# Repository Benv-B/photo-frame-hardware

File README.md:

# AirDrop ChLCD Photo Frame — Hardware

Open-source carrier board for a **ChLCD color e-paper frame with native iPhone AirDrop**.

The design connects a **XIAO ESP32-C5** to an **IRIS AW1005S102 panel and matching TCON**. It includes an NFC wake circuit, power latching and a three-AA battery input. NFC wakes the electronics; the photo is transferred through AirDrop.

- [Firmware and project introduction](https://github.com/Benv-B/ESP32Drop)
- [KiCad project and assembly notes](hardware/iris_xiao_c5_revC) — use KiCad 10.0.6 or a compatible newer version.
- [Schematic PDF](hardware/iris_xiao_c5_revC/output/IRIS_C5_RevC_schematic.pdf) · [BOM](hardware/iris_xiao_c5_revC/output/BOM.csv) · [Gerbers](hardware/iris_xiao_c5_revC/output/gerbers)

The prototype has displayed photos received through AirDrop. Battery runtime and the complete NFC wake → display → shutdown cycle still need validation. Read the assembly notes for FPC orientation and the JP1 battery/USB configuration.

Original carrier design: [CERN-OHL-P-2.0](LICENSE). Project scripts: [0BSD](LICENSES/0BSD.txt). [Third-party library credits](THIRD_PARTY_NOTICES.md). IRIS panel/TCON internals, vendor firmware and waveforms are not included. Development and documentation were assisted by AI.

## 中文

这是 **AirDrop ChLCD 彩色电子纸相框**的自制载板：XIAO ESP32-C5 主控，连接 IRIS 屏幕和配套 TCON，带 NFC 唤醒、电源锁存和三节 AA 电池输入。

**KiCad、原理图、BOM、Gerbers 和配套固件均已开放。** 样机已完成 AirDrop 照片显示；续航和完整唤醒/断电流程仍需验证。ChLCD 属于胆甾相液晶显示，与 Spectra 6 的电泳技术不同。

装配前请看[接线说明](hardware/iris_xiao_c5_revC/README.md)。本仓库开源自制载板，不包含商用屏幕/TCON 内部固件和波形。

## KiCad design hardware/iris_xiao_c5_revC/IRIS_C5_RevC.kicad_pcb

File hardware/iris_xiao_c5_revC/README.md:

## 用户改线后重新铺铜（2026-10-16）

当前 PCB 使用用户确认保存的主文件（2026-10-16 18:33:46），已由 KiCad 10.0.6 重新填充正、背面 GND 区。

635 个走线/过孔对象、66 个封装的位置及所有铜几何参数在铺铜前后一致；只重新计算铜区填充。H1–H4 另补充“仅 PCB 机械元素”属性，解决机械孔不属于原理图符号的提示，孔位和尺寸未变。DRC、未连接、原理图一致性问题均为 0，225 个电气引脚核对通过。详见 `output/pcb/copper_fill_audit.json`。

本次上传工程请使用 **KiCad 10.0.6 或更新兼容版本**。下文关于 KiCad 9 的描述是原始生成过程记录。正反面预览和 Gerber/钻孔文件已随当前板图重新导出；标准器件模型取自本机 KiCad 库，未提供模型的器件（含 XIAO）只显示焊盘。

# IRIS 智能相框载板 · Rev C

2026-10-16。三节一次性碱性 AA、XIAO ESP32-C5、用户已有 IRIS TCON 与39针排线，指定 FH26W-39S-0.3SHW(60) 连接器。RevC按用户确认改用 TPS61023，取消 PG 检测，保留 NFC 唤醒、电源保持和自动关机。RevB 工程保留在相邻目录。

## 本版改变

- U1 换为 **TPS61023DRLR / C919459**，六脚 SOT-563，同步升压、EN控制、真正关断。
- U3 换为 **NT3H2111W0FHKH / C710403**，XQFN8、1.6×1.6mm，中心金属区域不焊接。八个功能脚编号与原版本相同。
- 删除 PG 拉高电阻 R3、总线门控晶体管 Q6、PG 电平转换 Q8/R17。XIAO 的 D2/GPIO25 留空。
- U2.ON直接接 EN_LATCH；R15保持总线默认断开，Q7只由固件 BUS_EN 控制。没有追加电压检测芯片。
- R1=787kΩ/0.1%，R2=100kΩ/0.1%；L1改为顺络MWSA0518S-1R0MT（1µH，C408343）。PWM标称输出5.278V，PFM标称约5.33V，因此图中写“约5.3V”。电源网络名仍使用 `5V_BOOST`/`5V_SYS`，不是精确5.000V标称。

三张 A4 原理图按电源、NFC锁存、主控/FPC分组，组内直接连线、跨组网络标签。62个实体元件，较RevB减少4件。RevC属于电路修订，不能把其网表称为与RevB完全一致。

## 文件入口

- `IRIS_C5_RevC.kicad_pro`：保存的板图需 KiCad 10.0.6 或更新兼容版本，打开已有原理图无需运行生成脚本。
- `output/IRIS_C5_RevC_schematic.pdf`：三页原理图。
- `output/BOM.csv`：元件参数和封装；`PROCUREMENT.md`：采购证据及尚未锁定的物料。
- `output/native_netlist.xml`、`output/pin_connections.csv`：实际网表及逐引脚连接。
- `output/validation.json`、`output/ERC.json`：原生网表与设计清单核对、ERC结果。
- `output/revision_comparison.json`：与RevB相比的预期变更审计。
- `output/preview/`：原理图逐页渲染。
- `IRIS_C5_RevC.kicad_pcb`：已完成布线的双层 PCB，80×60mm；四个3.2mm非金属化安装孔。
- `output/pcb/board_top.png` / `board_bottom.png`：PCB 预览；不含未提供的器件三维模型。
- `output/pcb/top_copper.png` / `bottom_copper.png`：正、背面铜层与丝印，背面按翻板视角显示。
- `output/pcb/DRC.json` / `netlist_parity.json`：最终PCB检查与原理图逐引脚一致性报告。
- `output/gerbers/`：双层制板、钢网和PTH/NPTH钻孔文件，供首版样机使用。

## PCB 与装配

XIAO在左上，USB朝上板边；39针FPC在右边，排线插入方向朝板外。电池正负端在左侧，NFC外置线圈端子和手动唤醒按钮在下侧。升压功率环路先手工布线，信号布线完成后补齐双面接地过孔。主电源干线0.6–1.0mm，常规信号0.2mm，细间距焊盘局部0.15mm，最小铜间距0.15mm，常规过孔0.6/0.3mm。

板材可按双层FR-4、1.6mm厚、1oz铜起步。J3为0.3mm间距连接器，钢网按Hirose原厂0.10mm厚的开口尺寸制作；其铜和阻焊尺寸未改。XIAO底部GPIO5等焊盘也有接线，装配时需要焊接底部焊盘，不能仅焊两侧邮票孔。C10为DNP不装。外置NFC线圈需按实际结构调谐。

XIAO越过板边的USB外形和与焊盘冲突的模块外形线移至F.Fab，已同步本地封装库；模块铜焊盘、外形尺寸和电气连接保持不变。安装孔属于PCB机械元素，不增加电路BOM。最终DRC为0错误、0警告、0未连接；62个电气元件、225个引脚与原理图一致。

## 电源与工作过程

`3×AA → J1 → F1/Q1 → TPS61023 → TPS22975 → 5V_SYS → TCON 与 XIAO`

电池盒只接 J1 的 BAT+、BAT-。AA不能接XIAO的锂电BAT焊盘。XIAO 5V输入经过D1/JP1，D1阻止USB倒灌至公共电源；模块内置稳压器产生3.3V。TPS22975切换公共供电，Q2/R4用于关机放电，主控和TCON共用该供电。按TI手册§11，ON先于VIN有效不会损伤器件，但此时输出上升斜率不受CT保证；本版EN_LATCH同时开启升压与开关，保留C6作为样机调整位置，不能仅凭C6标称值认定满足TCON上升沿。

NFC射频场通过U3采能输出触发Q3/Q4锁存；后续由电池保持，不需要手机一直贴着。手机移开后，XIAO继续接收图片、刷新屏幕，完成后用PWR_OFF清除锁存。SW1为手动唤醒按钮。J2连接外置13.56MHz天线，C10默认不装，为实物调谐预留。

实际操作为：碰NFC唤醒 → 等设备启动 → 在iPhone选择照片并发送 → 刷新后关机。NFC不承担图片传输，也不自动替用户在iOS中选择照片。

## 主控引脚

| XIAO 焊盘 | 用途 |
|---|---|
| D0 / GPIO1 | PWR_OFF，高电平清除锁存 |
| D1 / GPIO0 | SPI_CS_N，经U5与33Ω串阻至J3.37 |
| D2 / GPIO25 | 不接，本版不读取PG |
| D3 / GPIO7 | BUS_EN，高电平接通SPI隔离开关 |
| D4 / GPIO23 | NFC SDA |
| D5 / GPIO24 | NFC SCL |
| D6 / GPIO11 | 不接，避免启动UART输出影响外设 |
| D7 / GPIO12 | TCON_INT，经U5接J3.24 |
| D8 / GPIO8 | SPI SCLK，经U5与33Ω至J3.34 |
| D9 / GPIO9 | SPI MISO，经U5接J3.36 |
| D10 / GPIO10 | SPI MOSI，经U5与33Ω至J3.35 |
| 底部焊盘16 / GPIO5 | BAT_ADC，测量锁存输出的分压，需校准压降 |

J3.1–6供电，7/10/13/16/19/22/25接地，31脚AGINGEN下拉；SPI模式不用的LVDS及指定NC脚留空。R21/R22在TCON侧提供CS默认高电平。FPC方向和排线两端映射以实物逐针核对。

## 固件配合

1. 启动先保持PWR_OFF=0、BUS_EN=0、SPI_CS_N=1。取消原PG_N检查；等待公共电源启动完成后再开启总线。首版可从100ms供电等待开始调试，最终以实测稳定时间确定，这不是PG检测的等效反馈。
2. 按IRIS应用说明完成TCON初始化、复位/唤醒和状态查询。原文复位后等待300ms、唤醒后5ms；10英寸刷新超时至少留15s。
3. ESP32Drop收图，转换为1024×768 BGR888，再按IRIS协议发送和刷新。完整像素帧2.25MiB；接收、解码和Wi-Fi仍需额外内存。2026-10-21 已完成 C5 AirDrop 到实屏的样机验证，详见固件仓库的 docs/iris-tcon.md。
4. 等TCON真实完成，再置BUS_EN=0。经NFC I²C读取RF_FIELD_PRESENT，确认手机场已消失至少500ms，再置PWR_OFF=1。U3.FD不用。
5. 添加接收超时、错误退出、看门狗和电池ADC判断。没有PG或新增硬件欠压锁定，因此软件不能假设电源在所有负载下都已经稳定。

USB调试时拔JP1。仅USB供XIAO、TCON未供电时必须保持BUS_EN=0；需要TCON工作时另外用电池/限流电源并按SW1开启。取消PG后，这项隔离由固件和调试操作负责，不能宣称有硬件自动联锁。

## 验证范围

225个实体引脚：188个连接、37个明确NC。原生KiCad网表与RevC冻结清单逐引脚比较；预期修订审计要求只有U1/U2/U3/U4/Q7/L1/R1修改、R3/R17/Q6/Q8删除，其余55件保持不变。最终原生ERC为0错误、0警告；原理图PDF均逐页查看。

2026-10-21 实板已完成色条和 iPhone 照片刷新；以下供电边界仍需进一步测量。TPS61023的3.7A为典型谷值开关限流，不是5V输出3.7A；整机实际启动/刷新电流和三AA压降需要样机验证，不承诺能覆盖屏幕资料中的3A浪涌。TCON要求5.0–5.5V、0.5–10ms电源边沿、断电间隔至少50ms；C6、放电R4、保险丝F1为首版值。

`validation/nfc_latch/`保留RevB锁存的ngspice验证，该部分电路未改。它只验证等效RF触发/清除等情形，不是实物NFC、TPS61023或TCON带载验证。`validation/before_layout/`是沿用的RevB历史资料，RevC当前结果以output目录为准。

## 复现

Windows下本次通过WSL Ubuntu的KiCad9.0.8生成。封装及符号随工程提供。`design_manifest.json`定义元件和连接；`layout_functional.py`控制原理图布局；`generate_schematic.py`生成原理图和BOM，已存在的.kicad_pro不覆盖。

直接打开已保存的KiCad工程即可查看和修改成品布线。工作目录内的`build_pcb.py`是初始放置/预布线脚本，运行会重建PCB，不能当作最终PCB的刷新命令；交付压缩包以已布线的原生PCB为准，只包含核对与原理图生成脚本。板图检查可运行`python3 validate_pcb.py`和`kicad-cli pcb drc --format json --output output/pcb/DRC.json IRIS_C5_RevC.kicad_pcb`。

```sh
python3 generate_schematic.py
kicad-cli sch export netlist --format kicadxml --output output/native_netlist.xml IRIS_C5_RevC.kicad_sch
kicad-cli sch erc --format json --output output/ERC.json IRIS_C5_RevC.kicad_sch
python3 validate_netlist.py
python3 compare_revision.py
kicad-cli sch export pdf --output output/IRIS_C5_RevC_schematic.pdf IRIS_C5_RevC.kicad_sch
```

依据：[TI TPS61023](https://www.ti.com/lit/ds/symlink/tps61023.pdf)、[TPS22975](https://www.ti.com/lit/ds/symlink/tps22975.pdf)、[NXP NT3H2111](https://www.nxp.com/docs/en/data-sheet/NT3H2111_2211.pdf)、[NXP采能说明](https://www.nxp.com/docs/en/application-note/AN11578.pdf)、[SN74CB3Q3245](https://www.ti.com/lit/ds/symlink/sn74cb3q3245.pdf)、Seeed官方C5电路与封装、Hirose图纸及用户提供的IRIS规格/应用说明。

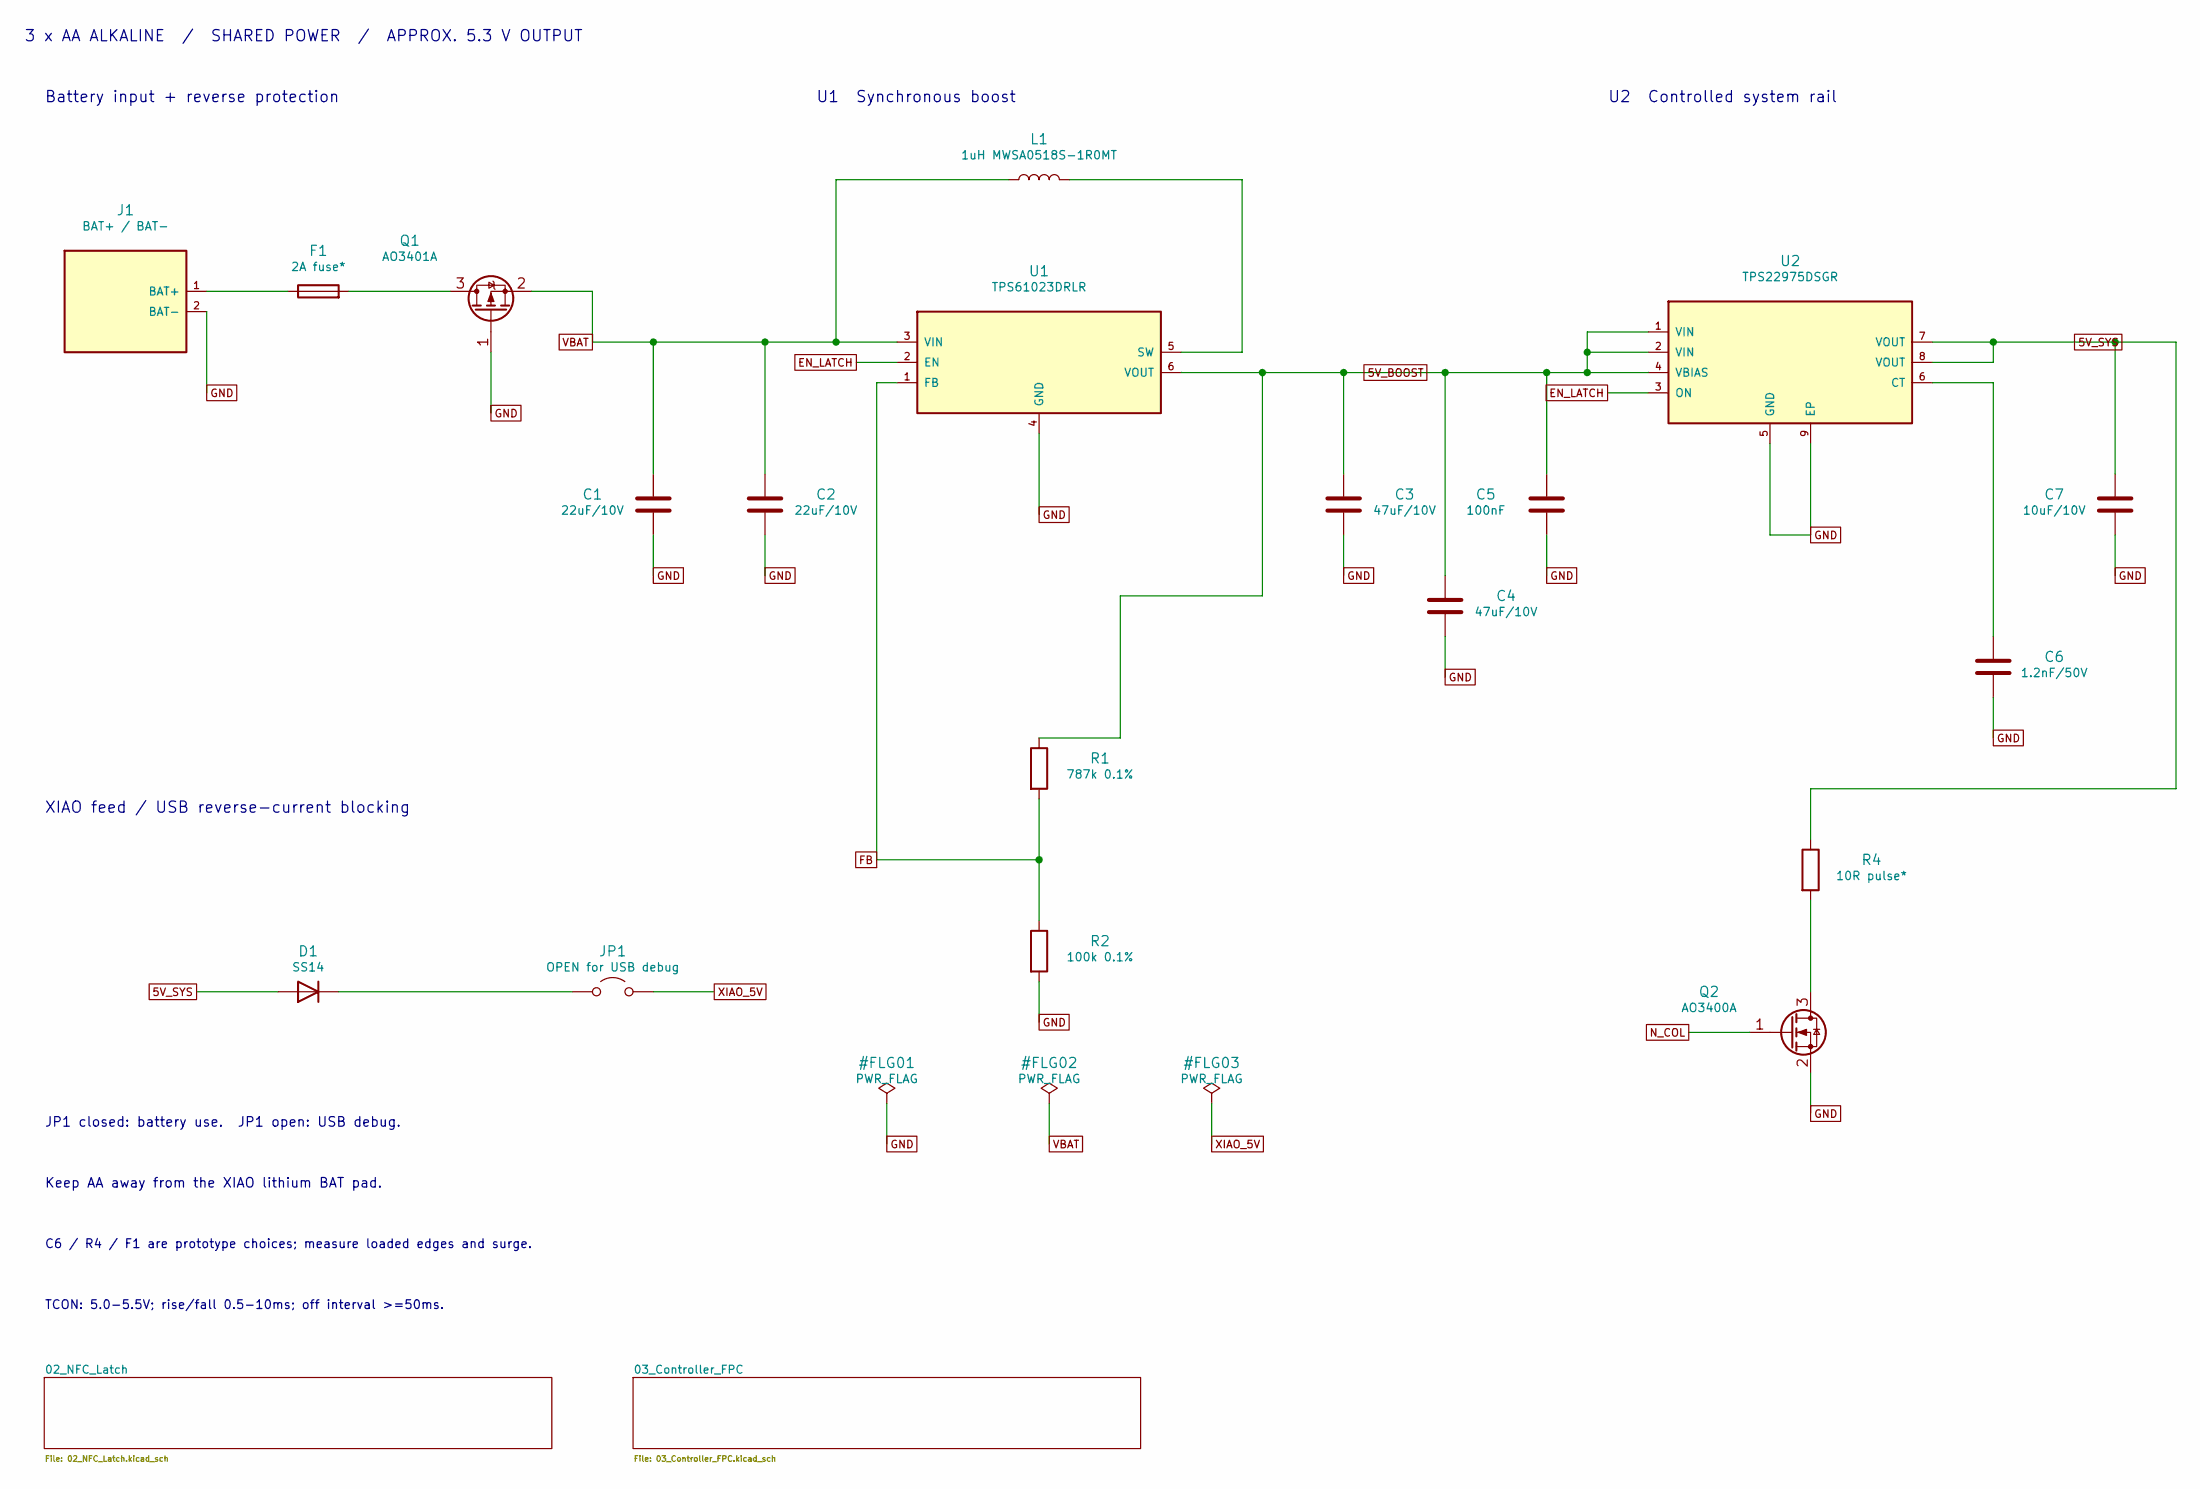
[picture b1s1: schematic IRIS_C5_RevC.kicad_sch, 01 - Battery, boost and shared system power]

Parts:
C1, C2: 22uF/10V; C_0805_2012Metric
C3, C4: 47uF/10V; C_1206_3216Metric
C5: 100nF; C_0603_1608Metric
C6: 1.2nF/50V; C_0603_1608Metric
C7: 10uF/10V; C_0805_2012Metric
D1: SS14; D_SMA
F1: 2A fuse*; Fuse_1206_3216Metric
J1: BAT+ / BAT-; Battery_Wire_2P
JP1: OPEN for USB debug; PinHeader_1x02_P2.54mm_Vertical
L1: 1uH MWSA0518S-1R0MT; Sunlord_MWSA0518S
Q1: AO3401A; SOT-23
Q2: AO3400A; SOT-23
R1: 787k 0.1%; R_0603_1608Metric
R2: 100k 0.1%; R_0603_1608Metric
R4: 10R pulse*; R_2512_6332Metric
U1: TPS61023DRLR; TI_DRL0006A
U2: TPS22975DSGR; Texas_DSG0008A_WSON-8-1EP_2x2mm_P0.5mm_EP0.9x1.6mm

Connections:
5V_BOOST: C3.1, C4.1, C5.1, R1.1, U1.6 (VOUT), U2.1 (VIN), U2.2 (VIN), U2.4 (VBIAS)
5V_SYS: C7.1, D1.2 (A), R4.1, U2.7 (VOUT), U2.8 (VOUT); also elsewhere on the board
EN_LATCH: U1.2 (EN), U2.3 (ON); also elsewhere on the board
FB: R1.2, R2.1, U1.1 (FB)
GND: C1.2, C2.2, C3.2, C4.2, C5.2, C6.2, C7.2, J1.2 (BAT-), Q1.1 (G), Q2.2 (S), R2.2, U1.4 (GND), U2.5 (GND), U2.9 (EP); also elsewhere on the board
N_COL: Q2.1 (G); also elsewhere on the board
unnamed: D1.1 (K), JP1.1 (A)
unnamed: F1.1, J1.1 (BAT+)
unnamed: F1.2, Q1.3 (D)
unnamed: Q2.3 (D), R4.2
unnamed: L1.2, U1.5 (SW)
unnamed: C6.1, U2.6 (CT)
VBAT: C1.1, C2.1, L1.1, Q1.2 (S), U1.3 (VIN); also elsewhere on the board
XIAO_5V: JP1.2 (B); also elsewhere on the board

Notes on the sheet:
3 x AA ALKALINE / SHARED POWER / APPROX. 5.3 V OUTPUT
Battery input + reverse protection
U1 Synchronous boost
U2 Controlled system rail
XIAO feed / USB reverse-current blocking
JP1 closed: battery use. JP1 open: USB debug.
Keep AA away from the XIAO lithium BAT pad.
C6 / R4 / F1 are prototype choices; measure loaded edges and surge.
TCON: 5.0-5.5V; rise/fall 0.5-10ms; off interval >=50ms.

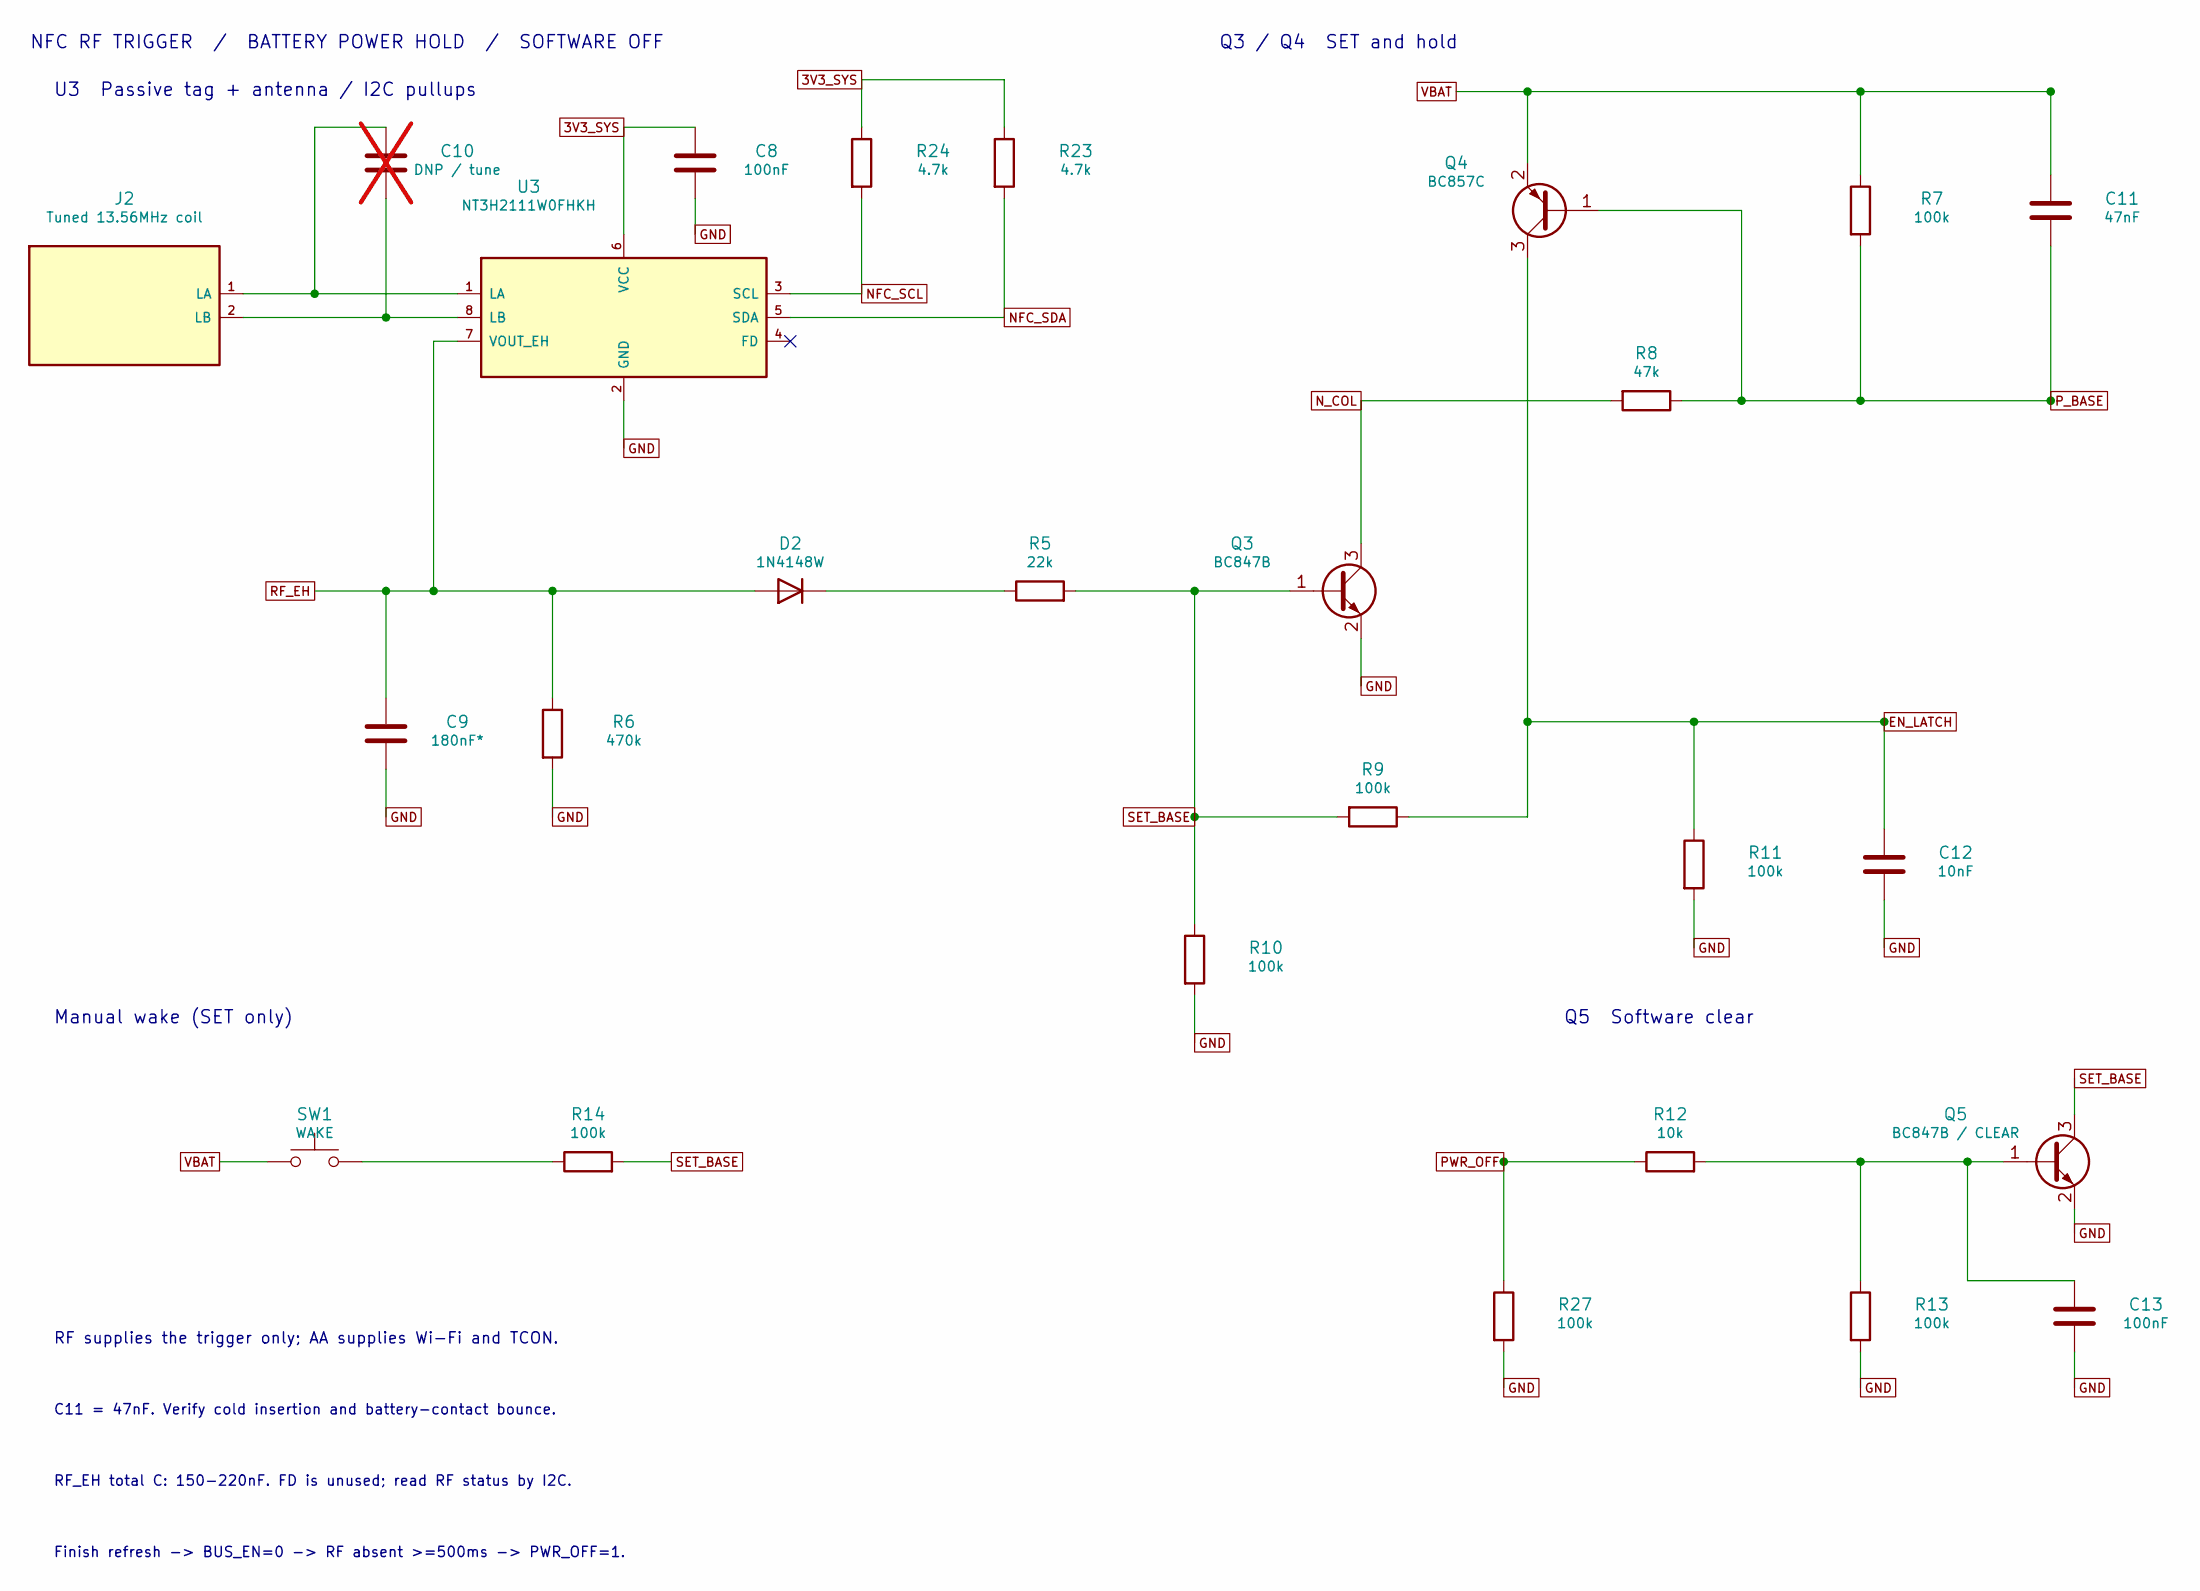
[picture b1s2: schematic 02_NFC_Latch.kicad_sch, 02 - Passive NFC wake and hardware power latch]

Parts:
C8, C13: 100nF; C_0603_1608Metric
C9: 180nF*; C_0603_1608Metric
C10: DNP / tune; C_0603_1608Metric; not fitted
C11: 47nF; C_0603_1608Metric
C12: 10nF; C_0603_1608Metric
D2: 1N4148W; D_SOD-123
J2: Tuned 13.56MHz coil; Battery_Wire_2P
Q3: BC847B; SOT-23
Q4: BC857C; SOT-23
Q5: BC847B / CLEAR; SOT-23
R5: 22k; R_0603_1608Metric
R6: 470k; R_0603_1608Metric
R7, R9, R10, R11, R13, R14, R27: 100k; R_0603_1608Metric
R8: 47k; R_0603_1608Metric
R12: 10k; R_0603_1608Metric
R23, R24: 4.7k; R_0603_1608Metric
SW1: WAKE; SW_SPST_TL3342
U3: NT3H2111W0FHKH; NXP_SOT902-3_XQFN8_1.6x1.6mm

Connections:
3V3_SYS: C8.1, R23.1, R24.1, U3.6 (VCC); also elsewhere on the board
EN_LATCH: C12.1, Q4.3 (C), R9.1, R11.1; also elsewhere on the board
GND: C8.2, C9.2, C12.2, C13.2, Q3.2 (E), Q5.2 (E), R6.2, R10.2, R11.2, R13.2, R27.2, U3.2 (GND); also elsewhere on the board
NFC_SCL: R24.2, U3.3 (SCL); also elsewhere on the board
NFC_SDA: R23.2, U3.5 (SDA); also elsewhere on the board
N_COL: Q3.3 (C), R8.2; also elsewhere on the board
unnamed: D2.1 (K), R5.1
unnamed: C10.1, J2.1 (LA), U3.1 (LA)
unnamed: C10.2, J2.2 (LB), U3.8 (LB)
unnamed: C13.1, Q5.1 (B), R12.2, R13.1
unnamed: R14.1, SW1.2
PWR_OFF: R12.1, R27.1; also elsewhere on the board
P_BASE: C11.2, Q4.1 (B), R7.2, R8.1
RF_EH: C9.1, D2.2 (A), R6.1, U3.7 (VOUT_EH)
SET_BASE: Q3.1 (B), Q5.3 (C), R5.2, R9.2, R10.1, R14.2
VBAT: C11.1, Q4.2 (E), R7.1, SW1.1; also elsewhere on the board

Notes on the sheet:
NFC RF TRIGGER / BATTERY POWER HOLD / SOFTWARE OFF
U3 Passive tag + antenna / I2C pullups
Q3 / Q4 SET and hold
Manual wake (SET only)
Q5 Software clear
RF supplies the trigger only; AA supplies Wi-Fi and TCON.
C11 = 47nF. Verify cold insertion and battery-contact bounce.
RF_EH total C: 150-220nF. FD is unused; read RF status by I2C.
Finish refresh -> BUS_EN=0 -> RF absent >=500ms -> PWR_OFF=1.

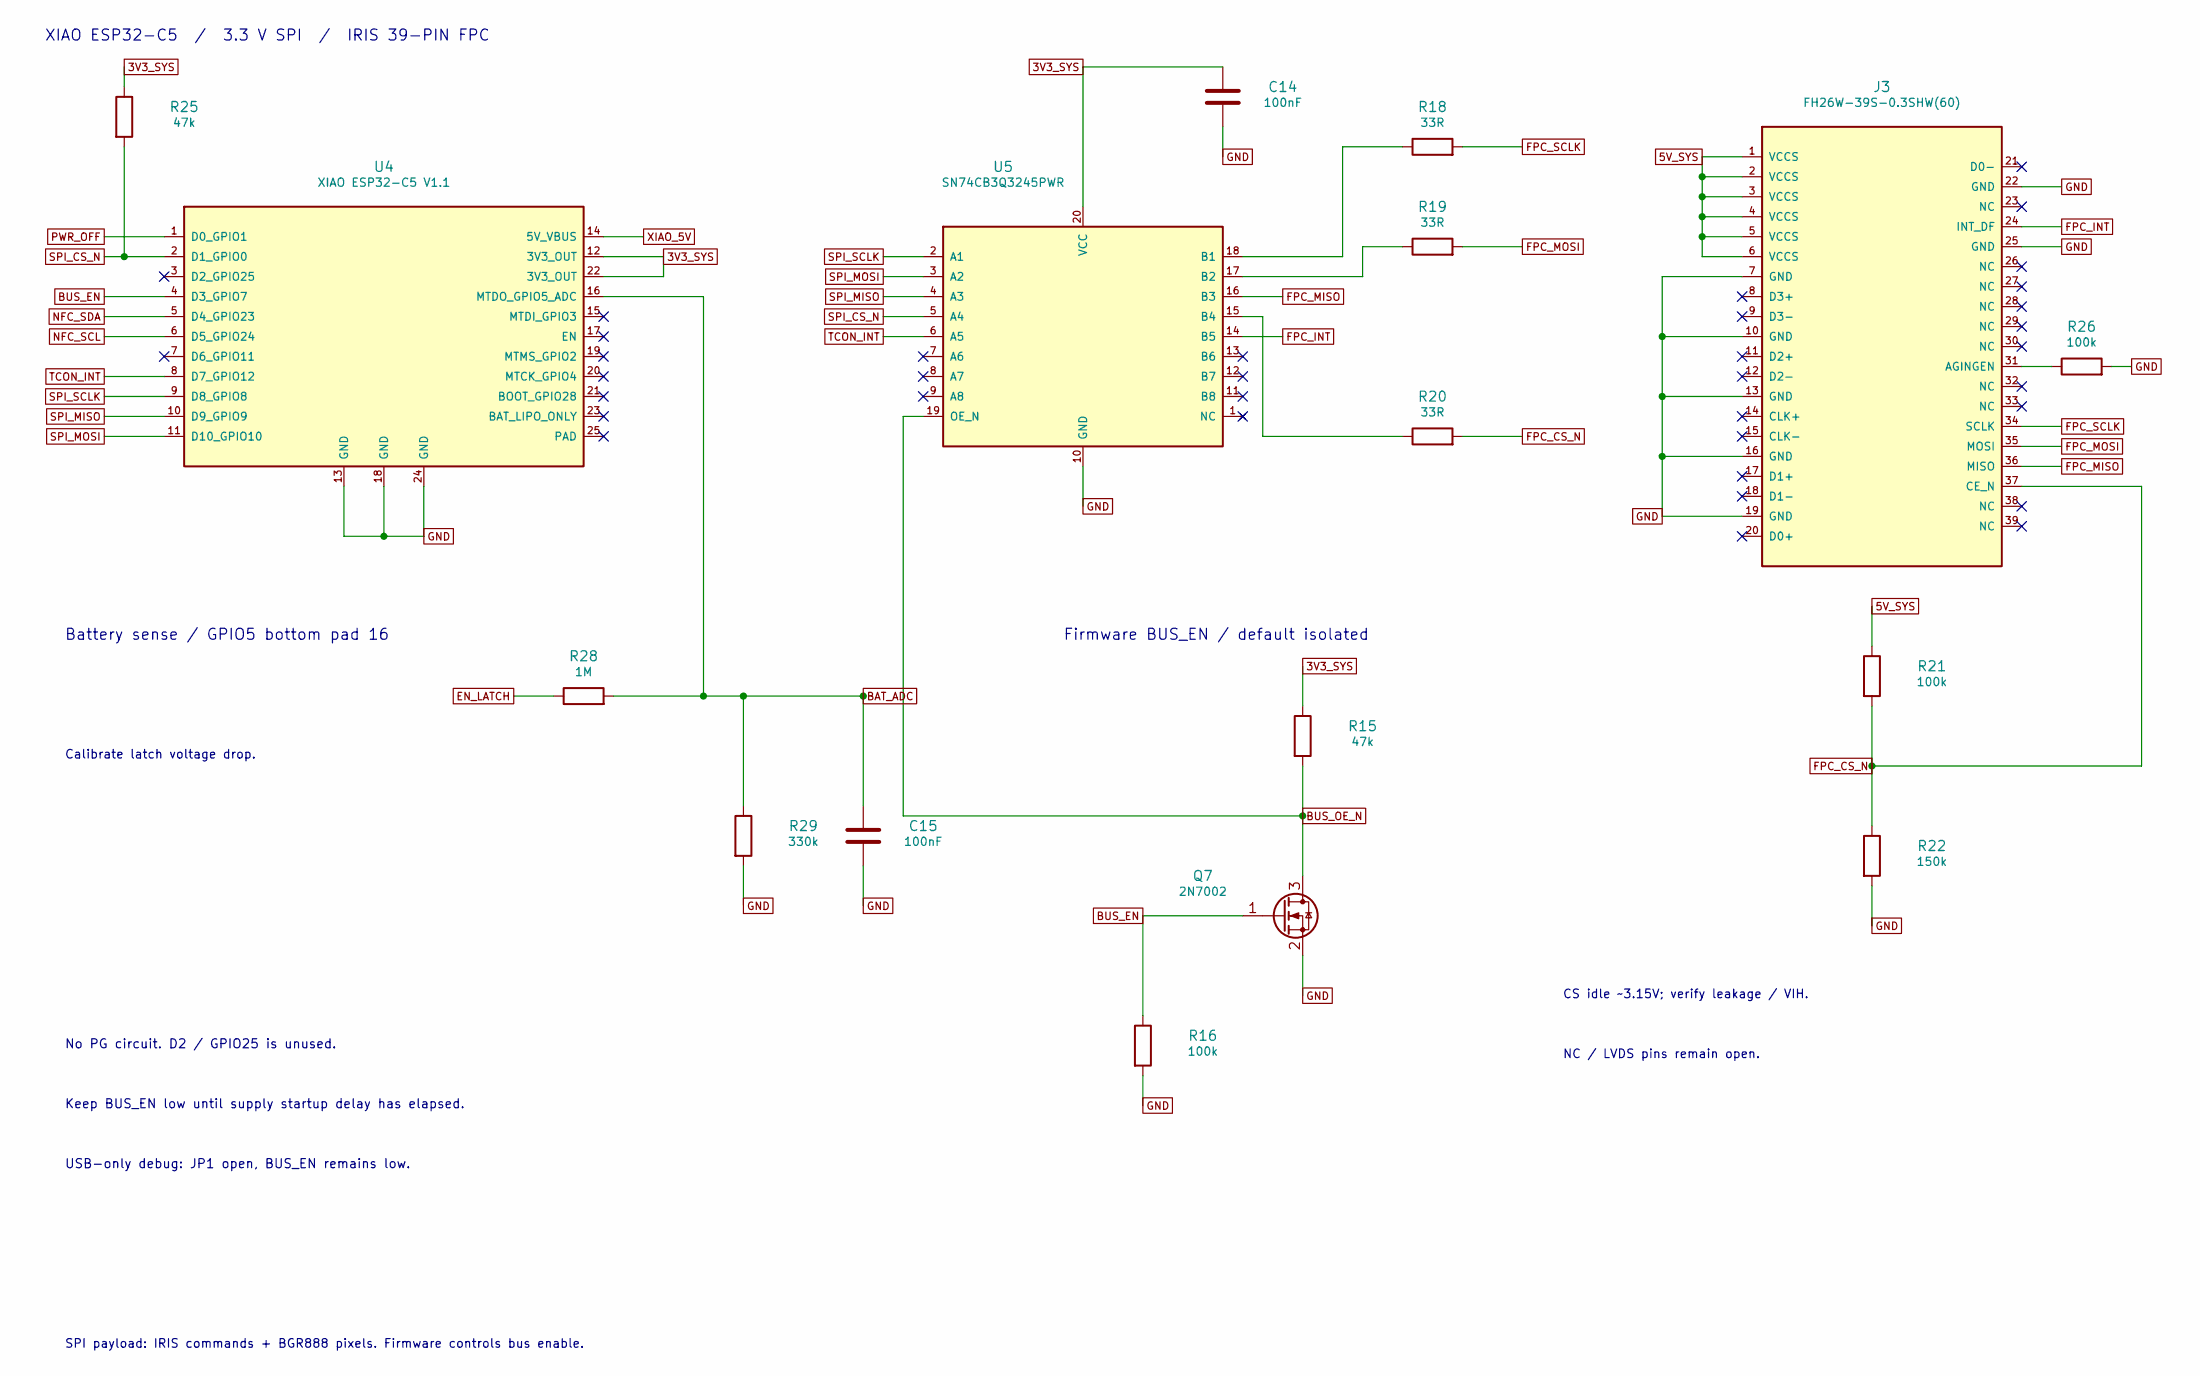
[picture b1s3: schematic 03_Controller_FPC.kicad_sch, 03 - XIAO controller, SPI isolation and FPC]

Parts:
C14, C15: 100nF; C_0603_1608Metric
J3: FH26W-39S-0.3SHW(60); Hirose_FH26-39S-0.3SHW_2Rows-39Pins-1MP_P0.60mm_Horizontal
Q7: 2N7002; SOT-23
R15, R25: 47k; R_0603_1608Metric
R16, R21, R26: 100k; R_0603_1608Metric
R18, R19, R20: 33R; R_0603_1608Metric
R22: 150k; R_0603_1608Metric
R28: 1M; R_0603_1608Metric
R29: 330k; R_0603_1608Metric
U4: XIAO ESP32-C5 V1.1; XIAO-ESP32-C5-SMD
U5: SN74CB3Q3245PWR; TSSOP-20_4.4x6.5mm_P0.65mm

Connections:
3V3_SYS: C14.1, R15.1, R25.1, U4.12 (3V3_OUT), U4.22 (3V3_OUT), U5.20 (VCC); also elsewhere on the board
5V_SYS: J3.1 (VCCS), J3.2 (VCCS), J3.3 (VCCS), J3.4 (VCCS), J3.5 (VCCS), J3.6 (VCCS), R21.1; also elsewhere on the board
BAT_ADC: C15.1, R28.2, R29.1, U4.16 (MTDO_GPIO5_ADC)
BUS_EN: Q7.1 (G), R16.1, U4.4 (D3_GPIO7)
BUS_OE_N: Q7.3 (D), R15.2, U5.19 (OE_N)
EN_LATCH: R28.1; also elsewhere on the board
FPC_CS_N: J3.37 (CE_N), R20.2, R21.2, R22.1
FPC_INT: J3.24 (INT_DF), U5.14 (B5)
FPC_MISO: J3.36 (MISO), U5.16 (B3)
FPC_MOSI: J3.35 (MOSI), R19.2
FPC_SCLK: J3.34 (SCLK), R18.2
GND: C14.2, C15.2, J3.7 (GND), J3.10 (GND), J3.13 (GND), J3.16 (GND), J3.19 (GND), J3.22 (GND), J3.25 (GND), Q7.2 (S), R16.2, R22.2, R26.2, R29.2, U4.13 (GND), U4.18 (GND), U4.24 (GND), U5.10 (GND); also elsewhere on the board
NFC_SCL: U4.6 (D5_GPIO24); also elsewhere on the board
NFC_SDA: U4.5 (D4_GPIO23); also elsewhere on the board
unnamed: J3.31 (AGINGEN), R26.1
unnamed: R18.1, U5.18 (B1)
unnamed: R19.1, U5.17 (B2)
unnamed: R20.1, U5.15 (B4)
PWR_OFF: U4.1 (D0_GPIO1); also elsewhere on the board
SPI_CS_N: R25.2, U4.2 (D1_GPIO0), U5.5 (A4)
SPI_MISO: U4.10 (D9_GPIO9), U5.4 (A3)
SPI_MOSI: U4.11 (D10_GPIO10), U5.3 (A2)
SPI_SCLK: U4.9 (D8_GPIO8), U5.2 (A1)
TCON_INT: U4.8 (D7_GPIO12), U5.6 (A5)
XIAO_5V: U4.14 (5V_VBUS); also elsewhere on the board

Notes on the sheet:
XIAO ESP32-C5 / 3.3 V SPI / IRIS 39-PIN FPC
Battery sense / GPIO5 bottom pad 16
Calibrate latch voltage drop.
Firmware BUS_EN / default isolated
No PG circuit. D2 / GPIO25 is unused.
Keep BUS_EN low until supply startup delay has elapsed.
USB-only debug: JP1 open, BUS_EN remains low.
CS idle ~3.15V; verify leakage / VIH.
NC / LVDS pins remain open.
SPI payload: IRIS commands + BGR888 pixels. Firmware controls bus enable.

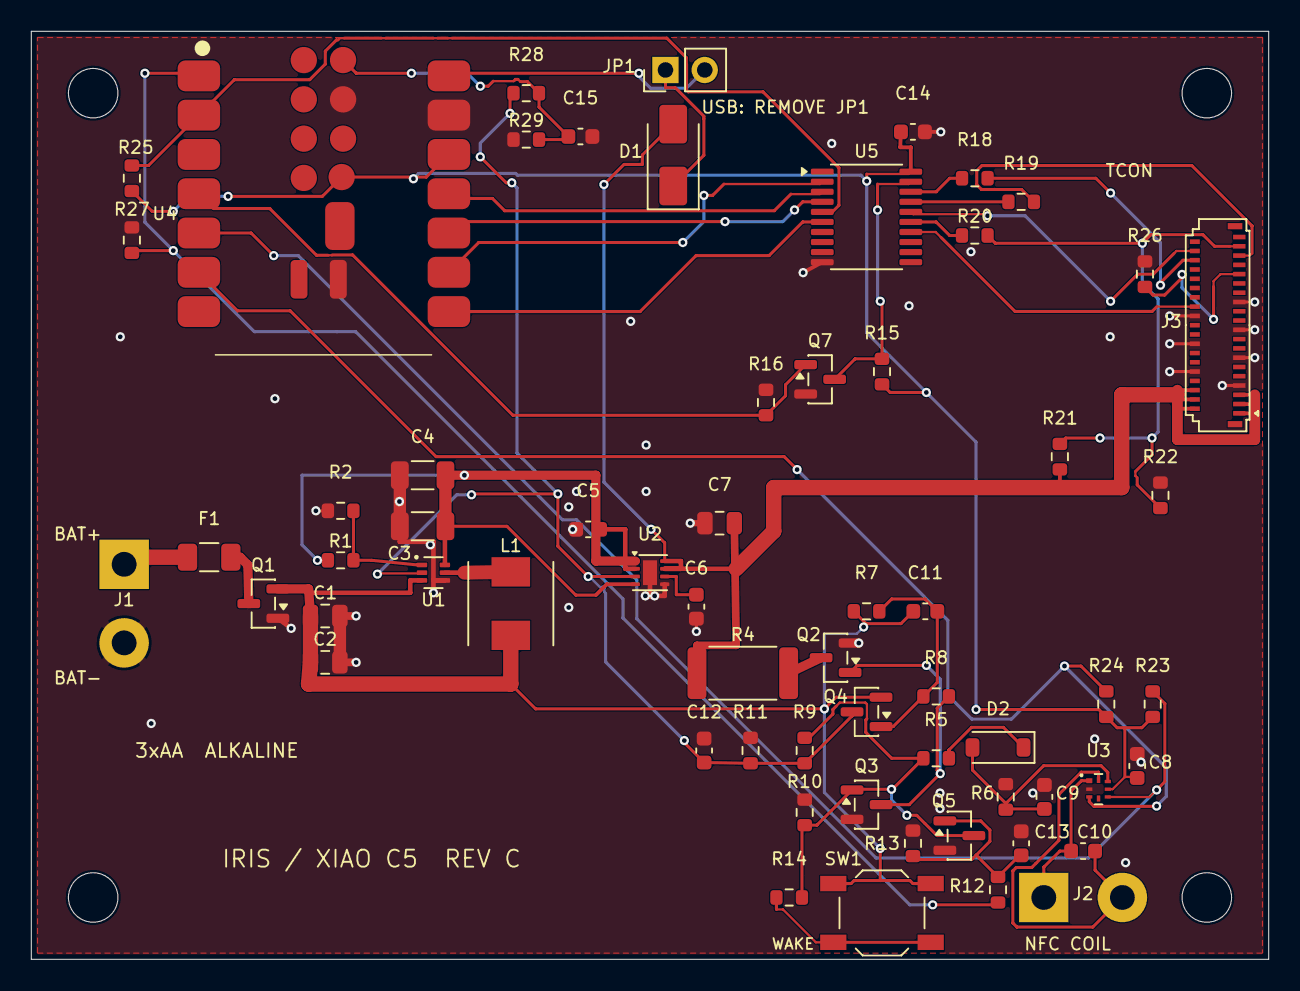
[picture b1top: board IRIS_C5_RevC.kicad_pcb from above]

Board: 2 copper layers, 80.0 x 60.0 mm, 66 parts (0 on the bottom side), 43 nets.

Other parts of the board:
H1, H2, H3, H4: MountingHole_3.2mm_M3

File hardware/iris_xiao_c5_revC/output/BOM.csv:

Reference,Value,Footprint,Sheet,Notes
J1,BAT+ / BAT-,IRIS_Local:Battery_Wire_2P,1,
F1,2A fuse*,Fuse:Fuse_1206_3216Metric,1,Candidate; verify fuse pulse I2t with measured TCON inrush
Q1,AO3401A,Package_TO_SOT_SMD:SOT-23,1,Reverse polarity protection: source is protected side
U1,TPS61023DRLR,IRIS_Local:TI_DRL0006A,1,C919459; six-pin TI DRL0006A; no PG; 0.595V nominal feedback
L1,1uH MWSA0518S-1R0MT,IRIS_Local:Sunlord_MWSA0518S,1,"C408343; Sunlord, Irms 8A, Isat 9A, DCR17mOhm; original land pattern"
C1,22uF/10V,Capacitor_SMD:C_0805_2012Metric,1,
C2,22uF/10V,Capacitor_SMD:C_0805_2012Metric,1,
U2,TPS22975DSGR,IRIS_Local:Texas_DSG0008A_WSON-8-1EP_2x2mm_P0.5mm_EP0.9x1.6mm,1,ON follows hardware latch directly; no power-good detector
C3,47uF/10V,Capacitor_SMD:C_1206_3216Metric,1,
C4,47uF/10V,Capacitor_SMD:C_1206_3216Metric,1,
C5,100nF,Capacitor_SMD:C_0603_1608Metric,1,
R1,787k 0.1%,Resistor_SMD:R_0603_1608Metric,1,PWM nominal 5.27765V; PFM nominal +1% ~5.33V
R2,100k 0.1%,Resistor_SMD:R_0603_1608Metric,1,
C7,10uF/10V,Capacitor_SMD:C_0805_2012Metric,1,
C6,1.2nF/50V,Capacitor_SMD:C_0603_1608Metric,1,
R4,10R pulse*,Resistor_SMD:R_2512_6332Metric,1,Pulse energy includes C*V^2/2 plus supply/discharge overlap (~2.76mJ/ms); validate actual waveforms and resistor pulse curve
Q2,AO3400A,Package_TO_SOT_SMD:SOT-23,1,N_COL high when latch OFF; verify discharge/load-switch order
D1,SS14,Diode_SMD:D_SMA,1,Anode at SYS; cathode toward XIAO. Blocks USB backfeed to SYS.
JP1,OPEN for USB debug,Connector_PinHeader_2.54mm:PinHeader_1x02_P2.54mm_Vertical,1,
J2,Tuned 13.56MHz coil,IRIS_Local:Battery_Wire_2P,2,Remote antenna; tune with screen/enclosure/ferrite
U3,NT3H2111W0FHKH,IRIS_Local:NXP_SOT902-3_XQFN8_1.6x1.6mm,2,C710403; SOT902-3 XQFN8; no center solder pad; FD unused
C10,DNP / tune,Capacitor_SMD:C_0603_1608Metric,2,
C8,100nF,Capacitor_SMD:C_0603_1608Metric,2,
R24,4.7k,Resistor_SMD:R_0603_1608Metric,2,
R23,4.7k,Resistor_SMD:R_0603_1608Metric,2,
C9,180nF*,Capacitor_SMD:C_0603_1608Metric,2,
R6,470k,Resistor_SMD:R_0603_1608Metric,2,
D2,1N4148W,Diode_SMD:D_SOD-123,2,
R5,22k,Resistor_SMD:R_0603_1608Metric,2,
Q3,BC847B,Package_TO_SOT_SMD:SOT-23,2,
Q4,BC857C,Package_TO_SOT_SMD:SOT-23,2,
R8,47k,Resistor_SMD:R_0603_1608Metric,2,
R7,100k,Resistor_SMD:R_0603_1608Metric,2,
C11,47nF,Capacitor_SMD:C_0603_1608Metric,2,
R9,100k,Resistor_SMD:R_0603_1608Metric,2,
R10,100k,Resistor_SMD:R_0603_1608Metric,2,
R11,100k,Resistor_SMD:R_0603_1608Metric,2,
C12,10nF,Capacitor_SMD:C_0603_1608Metric,2,
SW1,WAKE,Button_Switch_SMD:SW_SPST_TL3342,2,
R14,100k,Resistor_SMD:R_0603_1608Metric,2,
Q5,BC847B / CLEAR,Package_TO_SOT_SMD:SOT-23,2,
R12,10k,Resistor_SMD:R_0603_1608Metric,2,
R13,100k,Resistor_SMD:R_0603_1608Metric,2,
C13,100nF,Capacitor_SMD:C_0603_1608Metric,2,
R27,100k,Resistor_SMD:R_0603_1608Metric,2,
U4,XIAO ESP32-C5 V1.1,IRIS_Local:XIAO-ESP32-C5-SMD,3,
U5,SN74CB3Q3245PWR,Package_SO:TSSOP-20_4.4x6.5mm_P0.65mm,3,
J3,FH26W-39S-0.3SHW(60),IRIS_Local:Hirose_FH26-39S-0.3SHW_2Rows-39Pins-1MP_P0.60mm_Horizontal,3,
R25,47k,Resistor_SMD:R_0603_1608Metric,3,
R28,1M,Resistor_SMD:R_0603_1608Metric,3,
R29,330k,Resistor_SMD:R_0603_1608Metric,3,
C15,100nF,Capacitor_SMD:C_0603_1608Metric,3,
C14,100nF,Capacitor_SMD:C_0603_1608Metric,3,
R18,33R,Resistor_SMD:R_0603_1608Metric,3,
R19,33R,Resistor_SMD:R_0603_1608Metric,3,
R20,33R,Resistor_SMD:R_0603_1608Metric,3,
R15,47k,Resistor_SMD:R_0603_1608Metric,3,
Q7,2N7002,Package_TO_SOT_SMD:SOT-23,3,
R16,100k,Resistor_SMD:R_0603_1608Metric,3,
R26,100k,Resistor_SMD:R_0603_1608Metric,3,
R21,100k,Resistor_SMD:R_0603_1608Metric,3,
R22,150k,Resistor_SMD:R_0603_1608Metric,3,

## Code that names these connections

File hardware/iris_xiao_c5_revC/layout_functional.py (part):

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w(n,at(n,'U3',6),(76.2,26.67),(83.82,26.67),at(n,'C8',1));label(n,(76.2,26.67),'3V3_SYS',180);g(n,'C8',2,3.81);g(n,'U3',2)
add(n,'R24',101.6,30.48);add(n,'R23',116.84,30.48)
w(n,at(n,'R24',1),(101.6,21.59),(116.84,21.59),at(n,'R23',1));label(n,(101.6,21.59),'3V3_SYS',180)
w(n,at(n,'U3',3),(101.6,at(n,'U3',3)[1]),at(n,'R24',2));label(n,(101.6,at(n,'U3',3)[1]),'NFC_SCL')
w(n,at(n,'U3',5),(116.84,at(n,'U3',5)[1]),at(n,'R23',2));label(n,(116.84,at(n,'U3',5)[1]),'NFC_SDA')
add(n,'C9',50.8,91.44);add(n,'R6',68.58,91.44);add(n,'D2',93.98,76.2,180);add(n,'R5',120.65,76.2,90)
w(n,at(n,'U3',7),(55.88,at(n,'U3',7)[1]),(55.88,76.2),(43.18,76.2),at(n,'D2',2));j(n,(55.88,76.2));label(n,(43.18,76.2),'RF_EH',180)
for ref in ['C9','R6']:j(n,vto(n,ref,1,76.2));g(n,ref,2)
connect(n,'D2',1,'R5',1)
add(n,'Q3',152.4,76.2);add(n,'Q4',175.26,35.56,180)
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w(n,at(n,'Q4',1),(195.58,35.56),(195.58,55.88),at(n,'R8',1))
w(n,at(n,'R8',1),(228.6,55.88))
for ref in ['R7','C11']:j(n,vto(n,ref,2,55.88))
j(n,(195.58,55.88));label(n,(228.6,55.88),'P_BASE')
w(n,at(n,'R8',2),(154.94,55.88),at(n,'Q3',3));label(n,(154.94,55.88),'N_COL',180)
connect(n,'R5',2,'Q3',1);g(n,'Q3',2)
add(n,'R9',156.21,100.33,270);add(n,'R10',137.16,115.57)
w(n,at(n,'Q4',3),(172.72,100.33),at(n,'R9',1))
w(n,at(n,'R9',2),(137.16,100.33),(137.16,76.2));j(n,(137.16,76.2))
w(n,(137.16,100.33),at(n,'R10',1));j(n,(137.16,100.33));label(n,(137.16,100.33),'SET_BASE',180);g(n,'R10',2)
add(n,'R11',190.5,105.41);add(n,'C12',210.82,105.41)
w(n,(172.72,90.17),(210.82,90.17));j(n,(172.72,90.17));label(n,(210.82,90.17),'EN_LATCH')
for ref in ['R11','C12']:j(n,vto(n,ref,1,90.17));g(n,ref,2)
heading(n,15.24,121.92,'Manual wake (SET only)')
add(n,'SW1',43.18,137.16);add(n,'R14',72.39,137.16,90)
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port(n,'Q5',3,'SET_BASE','U',3.81);g(n,'Q5',2,2.54)
connect(n,'R12',2,'Q5',1);j(n,vto(n,'R13',1,137.16))
w(n,at(n,'C13',1),(219.71,at(n,'C13',1)[1]),(219.71,137.16));j(n,(219.71,137.16))
w(n,at(n,'R12',1),(170.18,137.16));label(n,(170.18,137.16),'PWR_OFF',180);j(n,vto(n,'R27',1,137.16))
for ref in ['R13','C13','R27']:g(n,ref,2,3.81)
n.text(15.24,156.21,'RF supplies the trigger only; AA supplies Wi-Fi and TCON.',1.2)
n.text(15.24,163.83,'C11 = 47nF. Verify cold insertion and battery-contact bounce.',1.1)
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add(c,'R28',81.28,101.6,90);add(c,'R29',101.6,119.38);add(c,'C15',116.84,119.38)
port(c,'R28',1,'EN_LATCH','L')
w(c,at(c,'U4',16),(96.52,at(c,'U4',16)[1]),(96.52,101.6),at(c,'R28',2))
w(c,(96.52,101.6),(116.84,101.6));j(c,(96.52,101.6));label(c,(116.84,101.6),'BAT_ADC')
for ref in ['R29','C15']:j(c,vto(c,ref,1,101.6));g(c,ref,2)
heading(c,15.24,93.98,'Battery sense / GPIO5 bottom pad 16')
c.text(15.24,109.22,'Calibrate latch voltage drop.',1.1)
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heading(c,142.24,93.98,'Firmware BUS_EN / default isolated')
add(c,'R15',172.72,106.68);add(c,'Q7',170.18,129.54)
port(c,'R15',1,'3V3_SYS','U');connect(c,'R15',2,'Q7',3)
w(c,at(c,'U5',19),(121.92,at(c,'U5',19)[1]),(121.92,116.84),(172.72,116.84));j(c,(172.72,116.84));label(c,(172.72,116.84),'BUS_OE_N')
g(c,'Q7',2)
add(c,'R16',152.4,146.05)
w(c,at(c,'Q7',1),(152.4,129.54),at(c,'R16',1));label(c,(152.4,129.54),'BUS_EN',180);g(c,'R16',2,3.81)
c.text(15.24,146.05,'No PG circuit. D2 / GPIO25 is unused.',1.15)
c.text(15.24,153.67,'Keep BUS_EN low until supply startup delay has elapsed.',1.15)
c.text(15.24,161.29,'USB-only debug: JP1 open, BUS_EN remains low.',1.15)
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add(c,'R26',271.78,at(c,'J3',31)[1],90);connect(c,'J3',31,'R26',1);port(c,'R26',2,'GND','R',2.54)
add(c,'R21',245.11,99.06);add(c,'R22',245.11,121.92)
port(c,'R21',1,'5V_SYS','U');connect(c,'R21',2,'R22',1);g(c,'R22',2)
w(c,at(c,'J3',37),(279.4,at(c,'J3',37)[1]),(279.4,110.49),(245.11,110.49));j(c,(245.11,110.49));label(c,(245.11,110.49),'FPC_CS_N',180)
c.text(205.74,139.7,'CS idle ~3.15V; verify leakage / VIH.',1.1)
c.text(205.74,147.32,'NC / LVDS pins remain open.',1.1)
c.text(15.24,184.15,'SPI payload: IRIS commands + BGR888 pixels. Firmware controls bus enable.',1.1)
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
